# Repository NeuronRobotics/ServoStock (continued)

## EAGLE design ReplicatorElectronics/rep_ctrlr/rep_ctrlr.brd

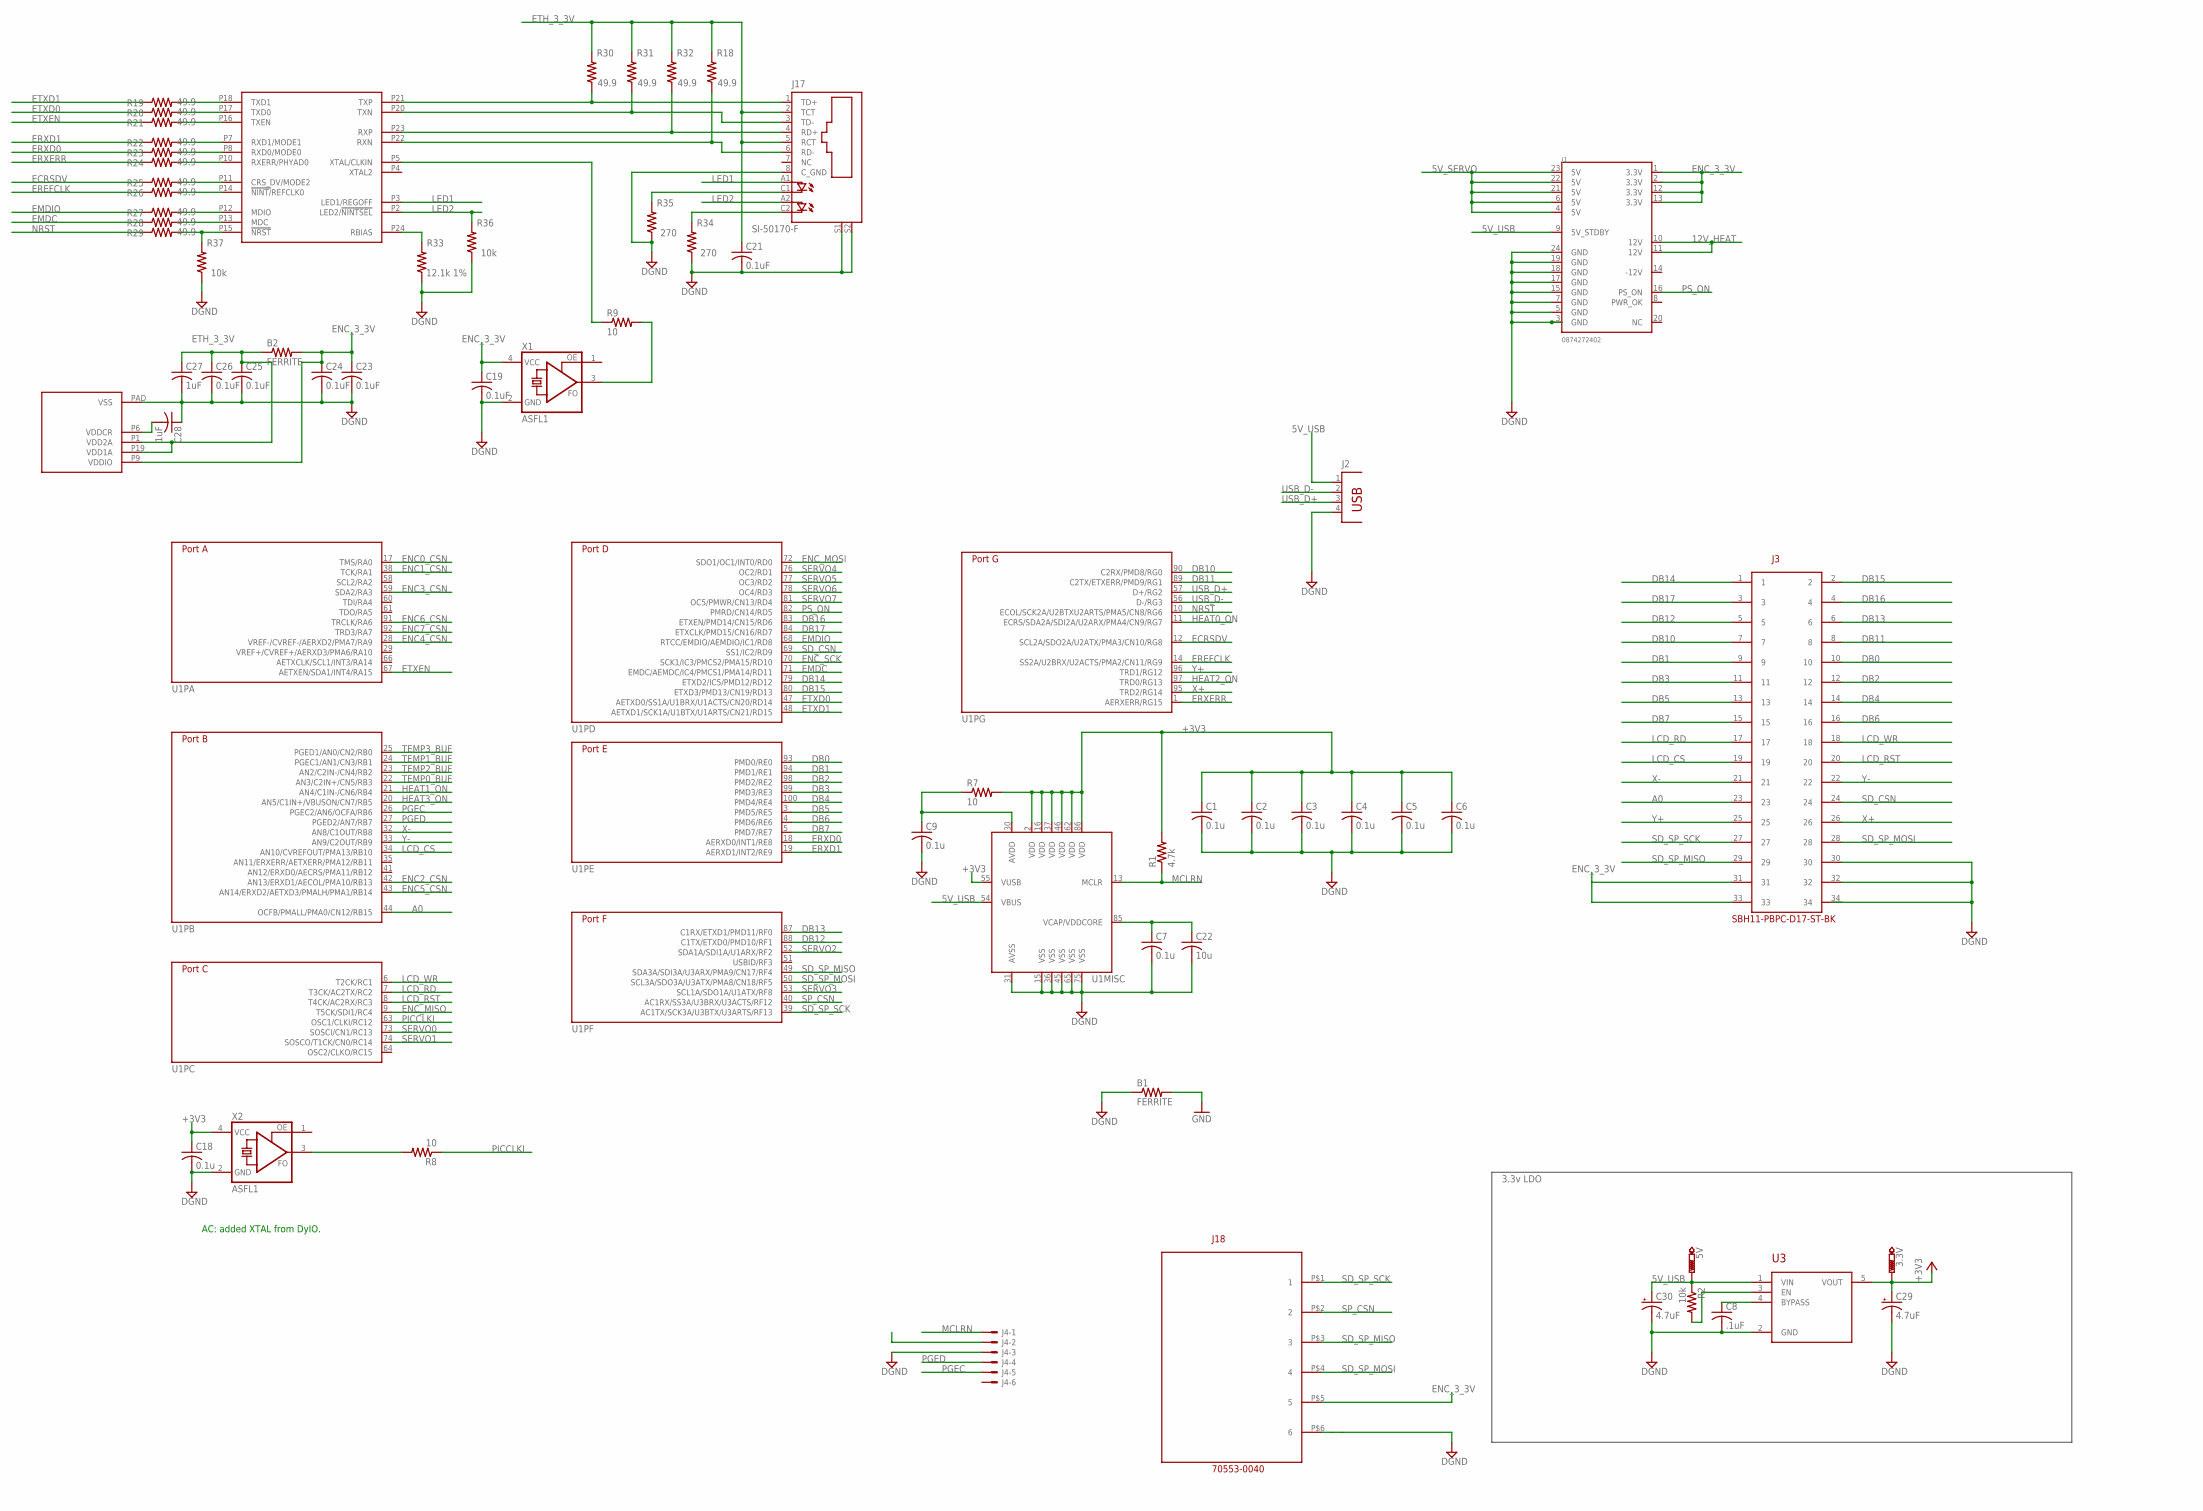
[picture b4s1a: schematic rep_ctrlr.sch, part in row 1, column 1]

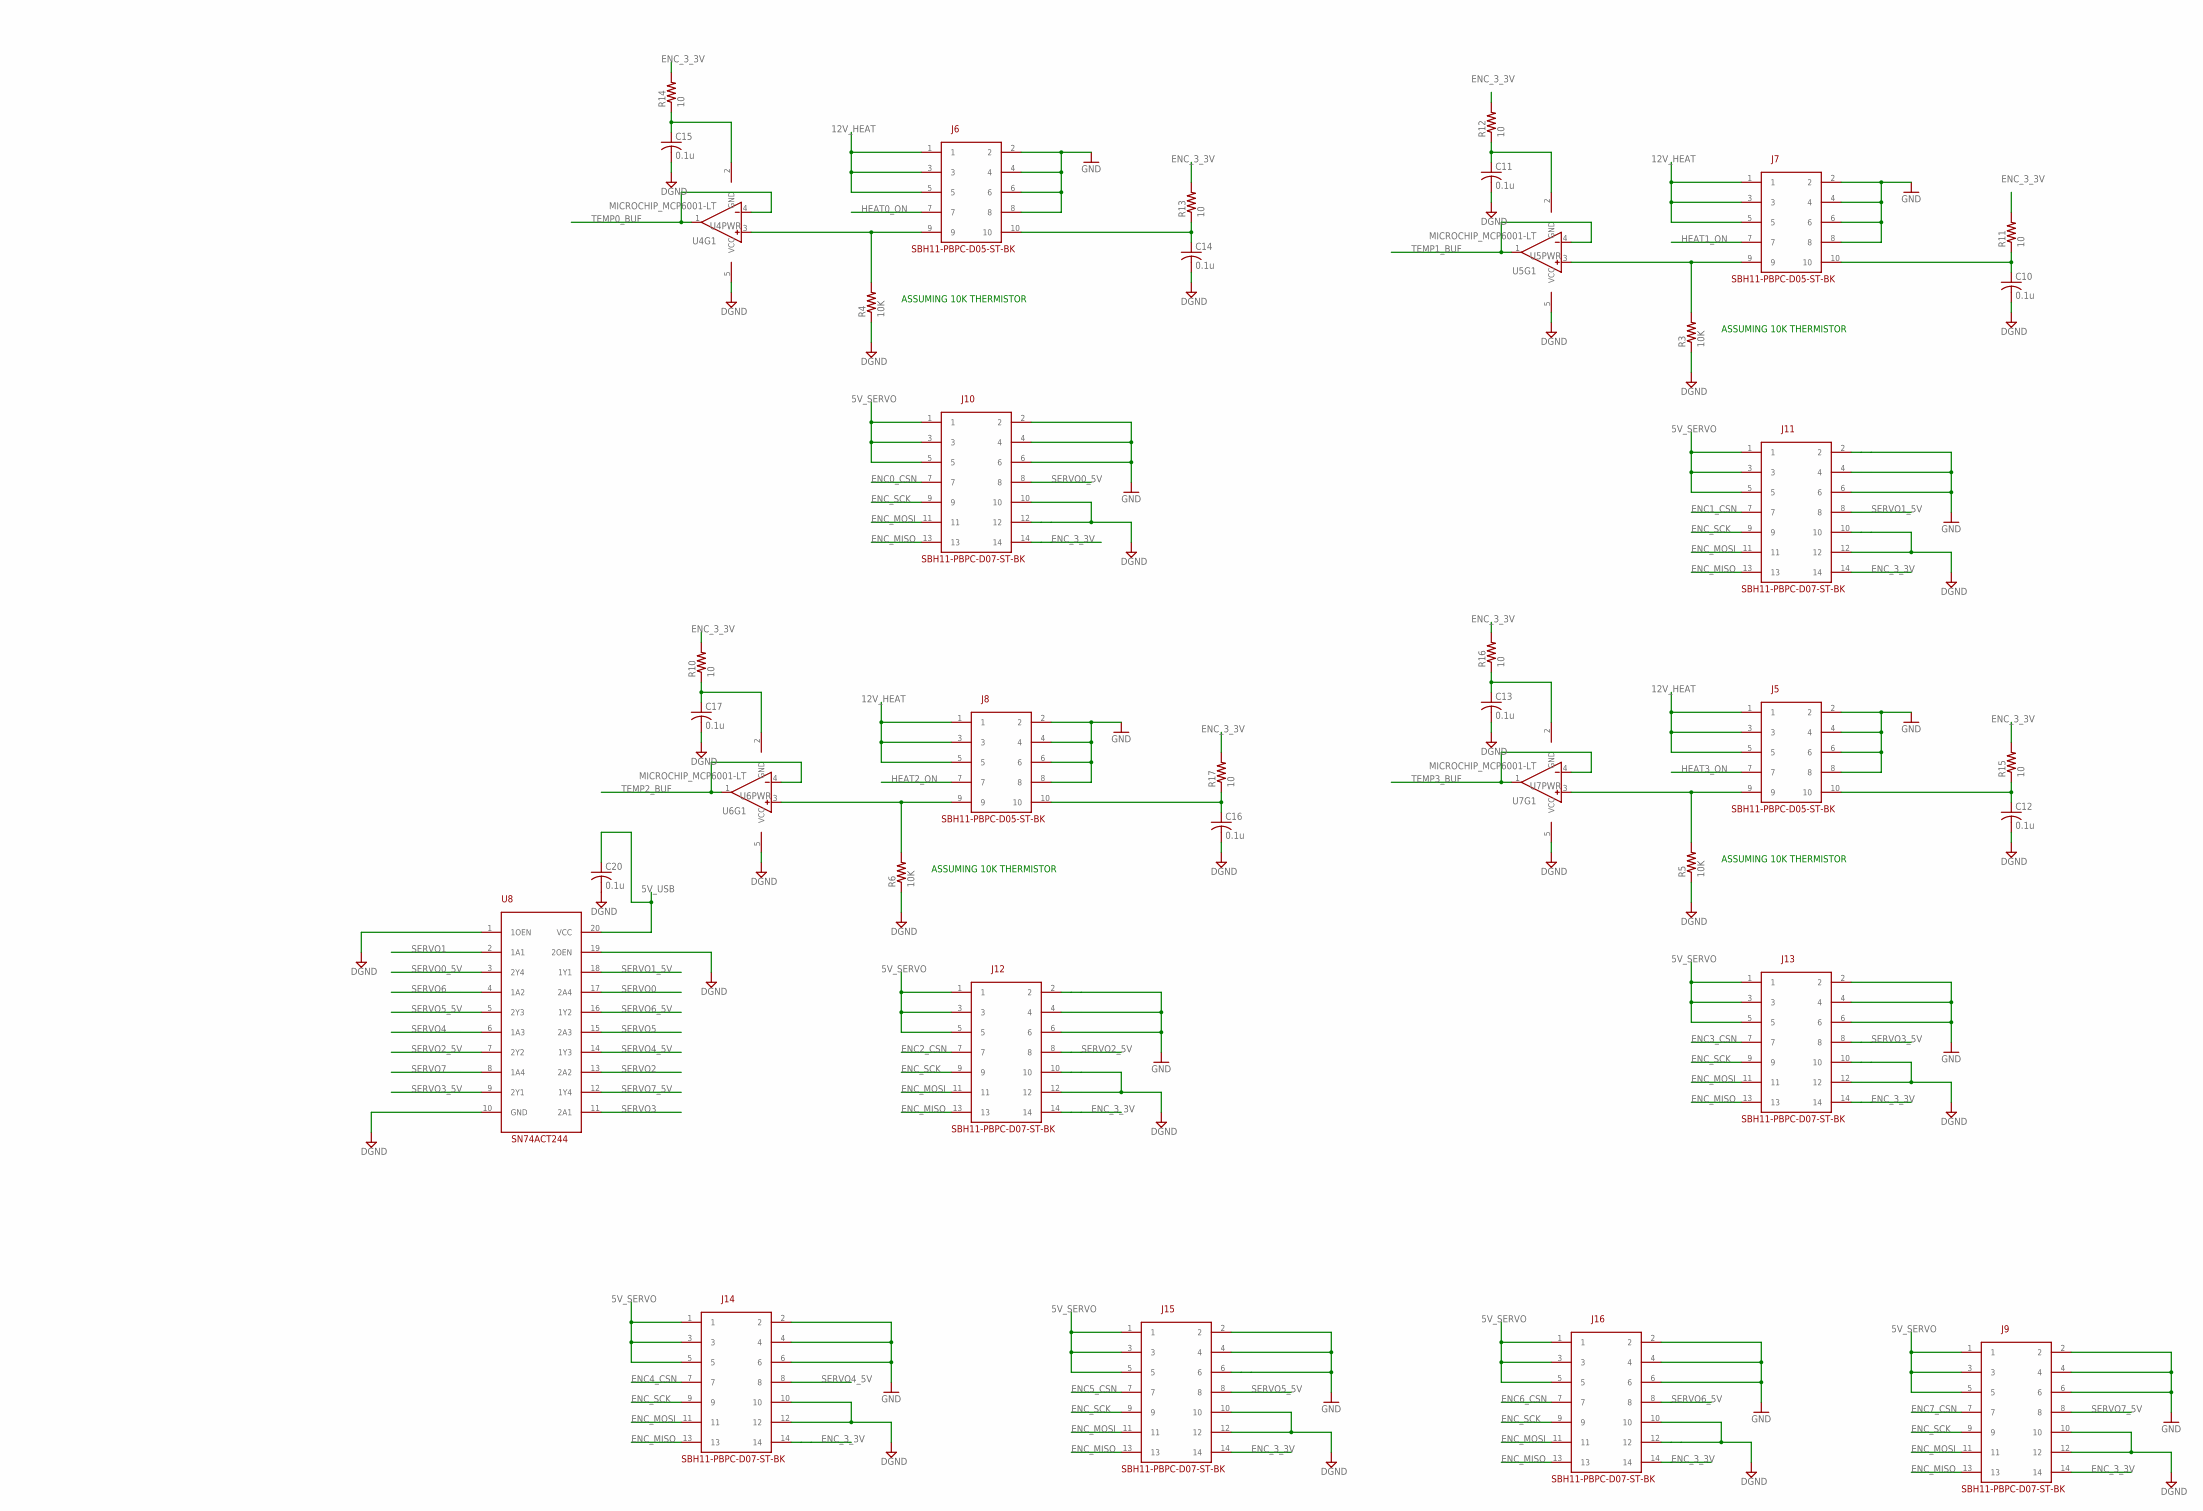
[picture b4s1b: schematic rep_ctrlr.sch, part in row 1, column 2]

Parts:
3.3V, 5V: PTR1TP14R; TP14R
B1, B2: FERRITE; R0805
C1, C2, C3, C4, C5, C6, C7, C9, C10, C11, C12, C13, C14, C15, C16, C17, C18, C20: 0.1u; C0402
C8: .1uF; C0402@1
C19, C21: 0.1uF; C0402
C22: 10u; C0603
C23, C24, C25, C26: 0.1uF; C0603
C27, C28: 1uF; C0603
C29, C30: 4.7uF; R/2012-12R
J1: 0874272402; ATX24_RIGHT_ANGLE
J2: PN61729
J3: SBH11-PBPC-D17-ST-BK
J4: 22-23-2061
J5, J6, J7, J8: SBH11-PBPC-D05-ST-BK
J9, J10, J11, J12, J13, J14, J15, J16: SBH11-PBPC-D07-ST-BK
J17: SI-50170-F; SI-50170
J18: 70553-0106; 70553-0109
R1: 4.7k; R0402
R2: 10k; R0402
R3, R4, R5, R6: 10K; R0402
R7, R8, R9, R10, R11, R12, R13, R14, R15, R16, R17: 10; R0402
R18, R19, R20, R21, R22, R23, R24, R25, R26, R27, R28, R29, R30, R31, R32: 49.9; R0603
R33: 12.1k 1%; R0603
R34, R35: 270; R0603
R36, R37: 10k; R0603
U1: MICROCHIP_PIC32MX7X5F256L-PF; MICROCHIP_TQ100-PF
U2: 8720A_PHY; QFN24
U3: LDS3985XX33; SOT23-5
U4, U5, U6, U7: MICROCHIP_MCP6001-LT; MICROCHIP_SC70-5-LT
U8: SN74ACT244; 20-SOIC
X1, X2: ASFL1; ASF

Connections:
5V_SERVO: J1.4 (5V), J1.6 (5V), J1.21 (5V), J1.22 (5V), J1.23 (5V), J9.1, J9.3, J9.5, J10.1, J10.3, J10.5, J11.1, J11.3, J11.5, J12.1, J12.3, J12.5, J13.1, J13.3, J13.5, J14.1, J14.3, J14.5, J15.1, J15.3, J15.5, J16.1, J16.3, J16.5
5V_USB: 5V.TP, C20.1, C30.+, J1.9 (5V_STDBY), J2.1, R2.1, U1.54 (VBUS), U3.1 (VIN), U8.20 (VCC)
12V_HEAT: J1.10 (12V), J1.11 (12V), J5.1, J5.3, J5.5, J6.1, J6.3, J6.5, J7.1, J7.3, J7.5, J8.1, J8.3, J8.5
+3V3: 3.3V.TP, C1.1, C2.1, C3.1, C4.1, C5.1, C6.1, C18.1, C29.+, J4.2, R1.2, R7.2, U1.2 (VDD), U1.16 (VDD), U1.37 (VDD), U1.46 (VDD), U1.55 (VUSB), U1.62 (VDD), U1.86 (VDD), U3.5 (VOUT), X2.4 (VCC)
A0: J3.23, U1.44 (OCFB/PMALL/PMA0/CN12/RB15)
DB0: J3.10, U1.93 (PMD0/RE0)
DB1: J3.9, U1.94 (PMD1/RE1)
DB2: J3.12, U1.98 (PMD2/RE2)
DB3: J3.11, U1.99 (PMD3/RE3)
DB4: J3.14, U1.100 (PMD4/RE4)
DB5: J3.13, U1.3 (PMD5/RE5)
DB6: J3.16, U1.4 (PMD6/RE6)
DB7: J3.15, U1.5 (PMD7/RE7)
DB10: J3.7, U1.90 (C2RX/PMD8/RG0)
DB11: J3.8, U1.89 (C2TX/ETXERR/PMD9/RG1)
DB12: J3.5, U1.88 (C1TX/ETXD0/PMD10/RF1)
DB13: J3.6, U1.87 (C1RX/ETXD1/PMD11/RF0)
DB14: J3.1, U1.79 (ETXD2/IC5/PMD12/RD12)
DB15: J3.2, U1.80 (ETXD3/PMD13/CN19/RD13)
DB16: J3.4, U1.83 (ETXEN/PMD14/CN15/RD6)
DB17: J3.3, U1.84 (ETXCLK/PMD15/CN16/RD7)
DGND: B1.1, C1.2, C2.2, C3.2, C4.2, C5.2, C6.2, C7.2, C8.2, C9.2, C10.2, C11.2, C12.2, C13.2, C14.2, C15.2, C16.2, C17.2, C18.2, C19.2, C20.2, C21.2, C22.2, C23.2, C24.2, C25.2, C26.2, C27.2, C28.1, C29.-, C30.-, J1.3 (GND), J1.5 (GND), J1.7 (GND), J1.15 (GND), J1.17 (GND), J1.18 (GND), J1.19 (GND), J1.24 (GND), J2.4, J3.30, J3.32, J4.3, J9.10, J9.12, J10.10, J10.12, J11.10, J11.12, J12.10, J12.12, J13.10, J13.12, J14.10, J14.12, J15.10, J15.12, J16.10, J16.12, J17.8 (C_GND), J17.S1, J17.S2, J18.P$6 (6), R3.1, R4.1, R5.1, R6.1, R33.1, R34.1, R35.1, R36.1, R37.1, U1.15 (VSS), U1.31 (AVSS), U1.36 (VSS), U1.45 (VSS), U1.65 (VSS), U1.75 (VSS), U2.PAD (VSS), U3.2 (GND), U4.5 (VCC), U5.5 (VCC), U6.5 (VCC), U7.5 (VCC), U8.1 (1OEN), U8.10 (GND), U8.19 (2OEN), X1.2 (GND), X2.2 (GND)
ECRSDV: R25.1, U1.12 (SCL2A/SDO2A/U2ATX/PMA3/CN10/RG8)
EMDC: R28.1, U1.71 (EMDC/AEMDC/IC4/PMCS1/PMA14/RD11)
EMDIO: R27.1, U1.68 (RTCC/EMDIO/AEMDIO/IC1/RD8)
ENC0_CSN: J10.7, U1.17 (TMS/RA0)
ENC1_CSN: J11.7, U1.38 (TCK/RA1)
ENC2_CSN: J12.7, U1.42 (AN13/ERXD1/AECOL/PMA10/RB13)
ENC3_CSN: J13.7, U1.59 (SDA2/RA3)
ENC4_CSN: J14.7, U1.28 (VREF-/CVREF-/AERXD2/PMA7/RA9)
ENC5_CSN: J15.7, U1.43 (AN14/ERXD2/AETXD3/PMALH/PMA1/RB14)
ENC6_CSN: J16.7, U1.91 (TRCLK/RA6)
ENC7_CSN: J9.7, U1.92 (TRD3/RA7)
ENC_3_3V: B2.2, C19.1, C23.1, C24.1, J1.1 (3.3V), J1.2 (3.3V), J1.12 (3.3V), J1.13 (3.3V), J3.31, J3.33, J9.14, J10.14, J11.14, J12.14, J13.14, J14.14, J15.14, J16.14, J18.P$5 (5), R10.2, R11.2, R12.2, R13.2, R14.2, R15.2, R16.2, R17.2, U2.P9 (VDDIO), X1.4 (VCC)
ENC_MISO: J9.13, J10.13, J11.13, J12.13, J13.13, J14.13, J15.13, J16.13, U1.9 (T5CK/SDI1/RC4)
ENC_MOSI: J9.11, J10.11, J11.11, J12.11, J13.11, J14.11, J15.11, J16.11, U1.72 (SDO1/OC1/INT0/RD0)
ENC_SCK: J9.9, J10.9, J11.9, J12.9, J13.9, J14.9, J15.9, J16.9, U1.70 (SCK1/IC3/PMCS2/PMA15/RD10)
EREFCLK: R26.1, U1.14 (SS2A/U2BRX/U2ACTS/PMA2/CN11/RG9)
ERXD0: R23.1, U1.18 (AERXD0/INT1/RE8)
ERXD1: R22.1, U1.19 (AERXD1/INT2/RE9)
ERXERR: R24.1, U1.1 (AERXERR/RG15)
ETH_3_3V: B2.1, C25.1, C26.1, C27.1, J17.2 (TCT), J17.5 (RCT), R18.2, R30.2, R31.2, R32.2, U2.P1 (VDD2A), U2.P19 (VDD1A)
ETXD0: R20.1, U1.47 (AETXD0/SS1A/U1BRX/U1ACTS/CN20/RD14)
ETXD1: R19.1, U1.48 (AETXD1/SCK1A/U1BTX/U1ARTS/CN21/RD15)
ETXEN: R21.1, U1.67 (AETXEN/SDA1/INT4/RA15)
GND: B1.2, J5.2, J5.4, J5.6, J5.8, J6.2, J6.4, J6.6, J6.8, J7.2, J7.4, J7.6, J7.8, J8.2, J8.4, J8.6, J8.8, J9.2, J9.4, J9.6, J10.2, J10.4, J10.6, J11.2, J11.4, J11.6, J12.2, J12.4, J12.6, J13.2, J13.4, J13.6, J14.2, J14.4, J14.6, J15.2, J15.4, J15.6, J16.2, J16.4, J16.6
HEAT0_ON: J6.7, U1.11 (ECRS/SDA2A/SDI2A/U2ARX/PMA4/CN9/RG7)
HEAT1_ON: J7.7, U1.21 (AN4/C1IN-/CN6/RB4)
HEAT2_ON: J8.7, U1.97 (TRD0/RG13)
HEAT3_ON: J5.7, U1.20 (AN5/C1IN+/VBUSON/CN7/RB5)
LCD_CS: J3.19, U1.34 (AN10/CVREFOUT/PMA13/RB10)
LCD_RD: J3.17, U1.7 (T3CK/AC2TX/RC2)
LCD_RST: J3.20, U1.8 (T4CK/AC2RX/RC3)
LCD_WR: J3.18, U1.6 (T2CK/RC1)
LED1: J17.A1 (A), U2.P3 (LED1/REGOFF)
LED2: J17.A2 (A1), R36.2, U2.P2 (LED2/!NINTSEL)
MCLRN: J4.1, R1.1, U1.13 (MCLR)
unnamed: R8.2, X2.3 (FO)
unnamed: C9.1, R7.1, U1.30 (AVDD)
unnamed: R9.2, X1.3 (FO)
unnamed: C7.1, C22.1, U1.85 (VCAP/VDDCORE)
unnamed: J7.9, R3.2, U5.3 (IN+)
unnamed: J5.9, R5.2, U7.3 (IN+)
unnamed: C12.1, J5.10, R15.1
unnamed: C10.1, J7.10, R11.1
unnamed: C11.1, R12.1, U5.2 (GND)
unnamed: C13.1, R16.1, U7.2 (GND)
unnamed: J6.9, R4.2, U4.3 (IN+)
unnamed: C14.1, J6.10, R13.1
unnamed: C15.1, R14.1, U4.2 (GND)
unnamed: J8.9, R6.2, U6.3 (IN+)
unnamed: C16.1, J8.10, R17.1
unnamed: C17.1, R10.1, U6.2 (GND)
unnamed: R19.2, U2.P18 (TXD1)
unnamed: R20.2, U2.P17 (TXD0)
unnamed: R21.2, U2.P16 (TXEN)
unnamed: R22.2, U2.P7 (RXD1/MODE1)
unnamed: R23.2, U2.P8 (RXD0/MODE0)
unnamed: R24.2, U2.P10 (RXERR/PHYAD0)
unnamed: R25.2, U2.P11 (CRS_DV/MODE2)
unnamed: R26.2, U2.P14 (!NINT/!REFCLK0)
unnamed: R27.2, U2.P12 (MDIO)
unnamed: R28.2, U2.P13 (MDC)
unnamed: R29.2, R37.2, U2.P15 (!NRST)
unnamed: J17.1 (TD+), R30.1, U2.P21 (TXP)
unnamed: J17.3 (TD-), R31.1, U2.P20 (TXN)
unnamed: J17.4 (RD+), R32.1, U2.P23 (RXP)
unnamed: J17.6 (RD-), R18.1, U2.P22 (RXN)
unnamed: R9.1, U2.P5 (XTAL/CLKIN)
unnamed: R2.2, U3.3 (EN)
unnamed: C8.1, U3.4 (BYPASS)
unnamed: J17.C1 (C), R35.2
unnamed: J17.C2 (C1), R34.2
unnamed: C28.2, U2.P6 (VDDCR)
unnamed: R33.2, U2.P24 (RBIAS)
NRST: R29.1, U1.10 (ECOL/SCK2A/U2BTXU2ARTS/PMA5/CN8/RG6)
PGEC: J4.5, U1.26 (PGEC2/AN6/OCFA/RB6)
PGED: J4.4, U1.27 (PGED2/AN7/RB7)
PICCLKI: R8.1, U1.63 (OSC1/CLKI/RC12)
PS_ON: J1.16 (PS_ON), U1.82 (PMRD/CN14/RD5)
SD_CSN: J3.24, U1.69 (SS1/IC2/RD9)
SD_SP_MISO: J3.29, J18.P$3 (3), U1.49 (SDA3A/SDI3A/U3ARX/PMA9/CN17/RF4)
SD_SP_MOSI: J3.28, J18.P$4 (4), U1.50 (SCL3A/SDO3A/U3ATX/PMA8/CN18/RF5)
SD_SP_SCK: J3.27, J18.P$1 (1), U1.39 (AC1TX/SCK3A/U3BTX/U3ARTS/RF13)
SERVO0: U1.73 (SOSCI/CN1/RC13), U8.17 (2A4)
SERVO0_5V: J10.8, U8.3 (2Y4)
SERVO1: U1.74 (SOSCO/T1CK/CN0/RC14), U8.2 (1A1)
SERVO1_5V: J11.8, U8.18 (1Y1)
SERVO2: U1.52 (SDA1A/SDI1A/U1ARX/RF2), U8.13 (2A2)
SERVO2_5V: J12.8, U8.7 (2Y2)
SERVO3: U1.53 (SCL1A/SDO1A/U1ATX/RF8), U8.11 (2A1)
SERVO3_5V: J13.8, U8.9 (2Y1)
SERVO4: U1.76 (OC2/RD1), U8.6 (1A3)
SERVO4_5V: J14.8, U8.14 (1Y3)
SERVO5: U1.77 (OC3/RD2), U8.15 (2A3)
SERVO5_5V: J15.8, U8.5 (2Y3)
SERVO6: U1.78 (OC4/RD3), U8.4 (1A2)
SERVO6_5V: J16.8, U8.16 (1Y2)
SERVO7: U1.81 (OC5/PMWR/CN13/RD4), U8.8 (1A4)
SERVO7_5V: J9.8, U8.12 (1Y4)
SP_CSN: J18.P$2 (2), U1.40 (AC1RX/SS3A/U3BRX/U3ACTS/RF12)
TEMP0_BUF: U1.22 (AN3/C2IN+/CN5/RB3), U4.1 (OUT), U4.4 (IN-)
TEMP1_BUF: U1.24 (PGEC1/AN1/CN3/RB1), U5.1 (OUT), U5.4 (IN-)
TEMP2_BUF: U1.23 (AN2/C2IN-/CN4/RB2), U6.1 (OUT), U6.4 (IN-)
TEMP3_BUF: U1.25 (PGED1/AN0/CN2/RB0), U7.1 (OUT), U7.4 (IN-)
USB_D+: J2.3, U1.57 (D+/RG2)
USB_D-: J2.2, U1.56 (D-/RG3)
X+: J3.26, U1.95 (TRD2/RG14)
X-: J3.21, U1.32 (AN8/C1OUT/RB8)
Y+: J3.25, U1.96 (TRD1/RG12)
Y-: J3.22, U1.33 (AN9/C2OUT/RB9)

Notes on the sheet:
ASSUMING 10K THERMISTOR
AC: added XTAL from DyIO.
3.3v LDO

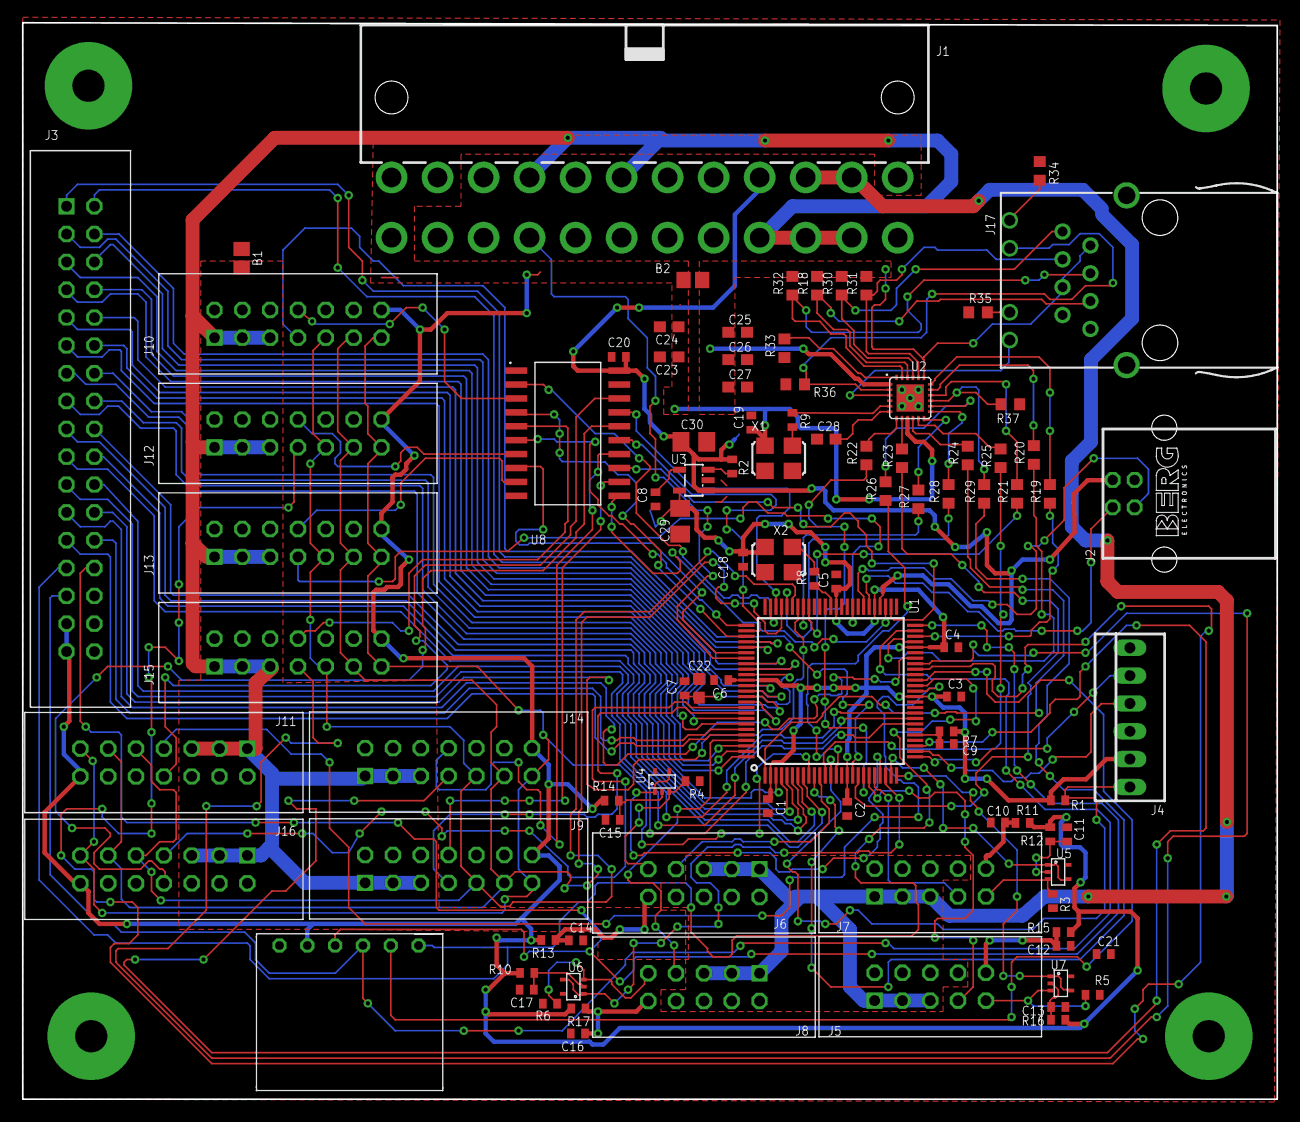
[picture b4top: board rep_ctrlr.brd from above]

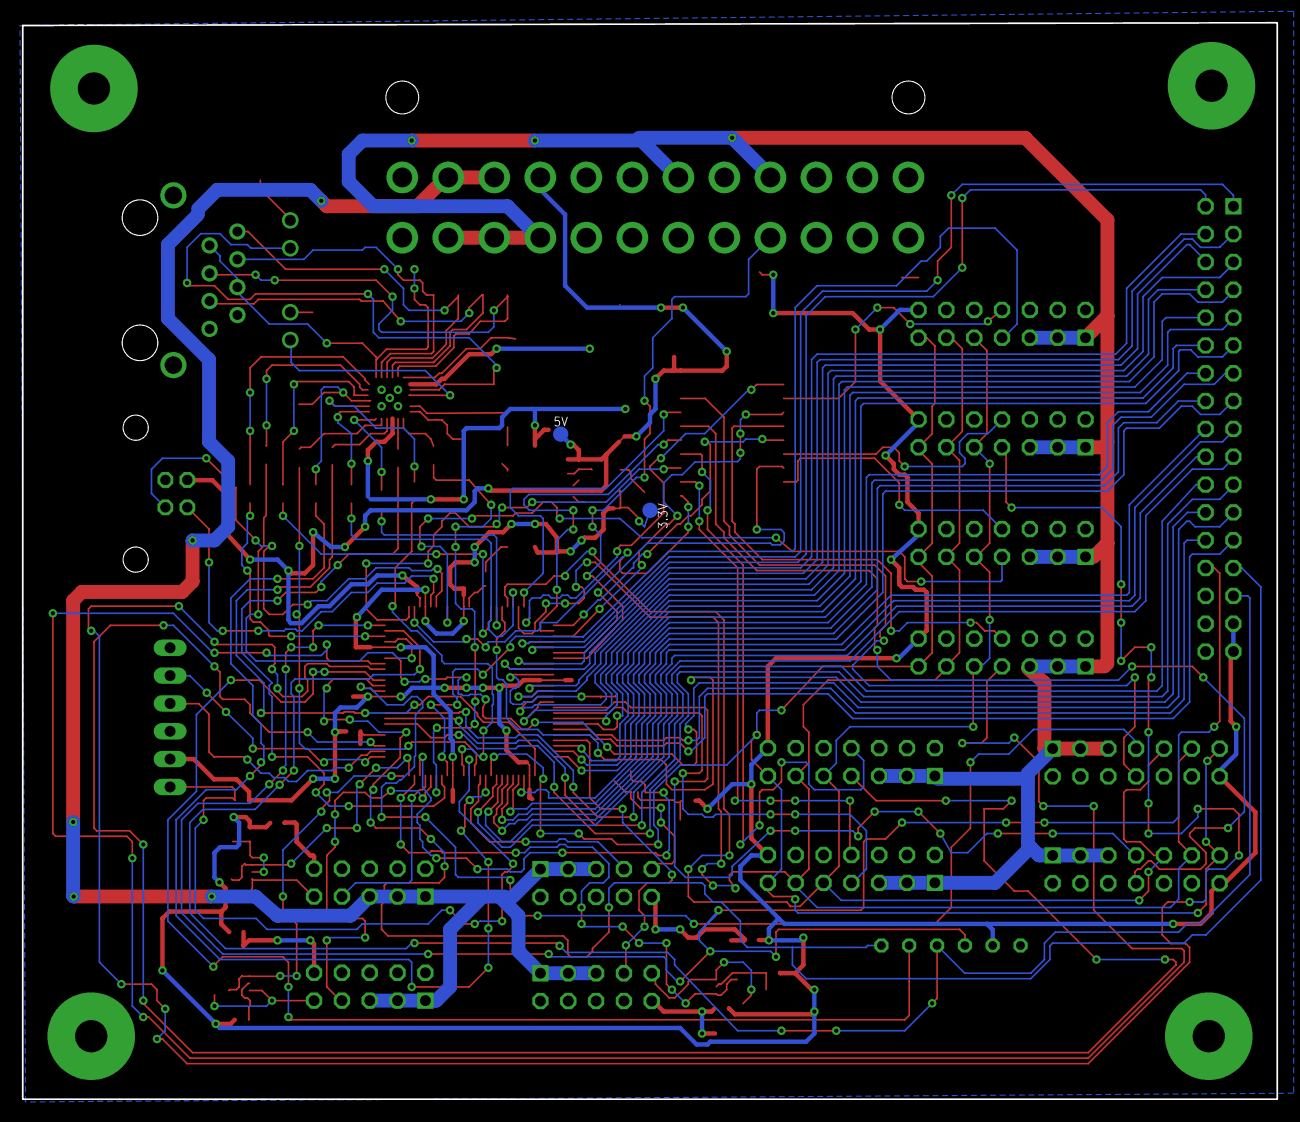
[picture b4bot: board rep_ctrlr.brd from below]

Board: 2 copper layers, 114.5 x 98.2 mm, 99 parts (2 on the bottom side), 131 nets.

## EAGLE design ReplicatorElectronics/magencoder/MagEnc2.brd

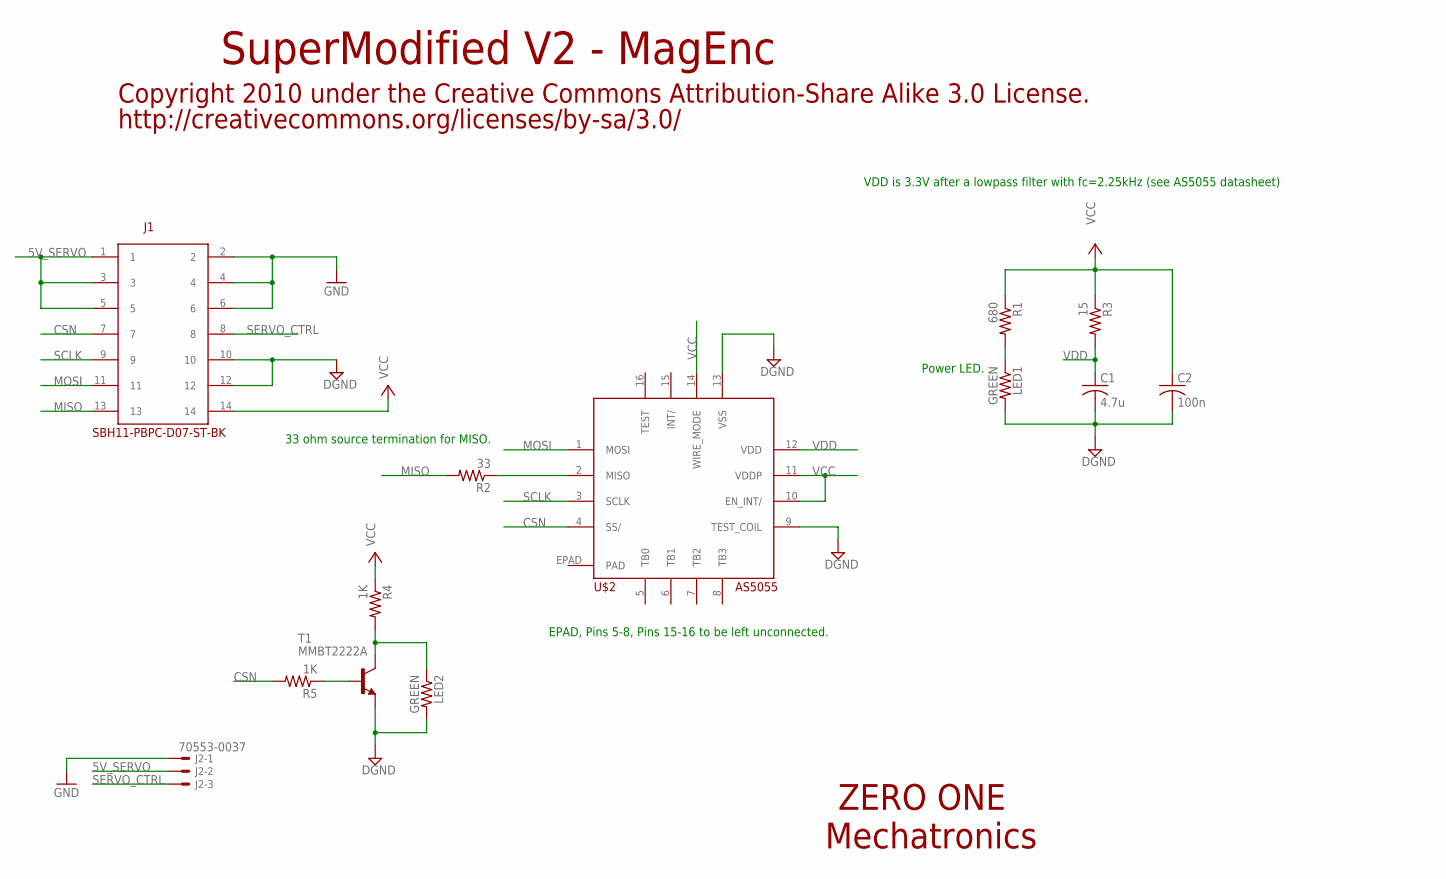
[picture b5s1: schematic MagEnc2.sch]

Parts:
C1: 4.7u; C0402
C2: 100n; C0402
J1: SBH11-PBPC-D07-ST-BK
J2: 70553-0037; 70553-03
LED1, LED2: GREEN; R0402
R1: 680; R0402
R2: 33; R0402
R3: 15; R0402
R4, R5: 1K; R0402
T1: MMBT2222A; SOT23-BEC
U$2: AS5055

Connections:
5V_SERVO: J1.1, J1.3, J1.5, J2.2
CSN: J1.7, R5.2, U$2.4 (SS/)
DGND: C1.2, C2.2, J1.10, J1.12, LED1.2, LED2.2, T1.E, U$2.9 (TEST_COIL), U$2.13 (VSS)
GND: J1.2, J1.4, J1.6, J2.1
MISO: J1.13, R2.2
MOSI: J1.11, U$2.1 (MOSI)
unnamed: LED1.1, R1.2
unnamed: LED2.1, R4.2, T1.C
unnamed: R5.1, T1.B
unnamed: R2.1, U$2.2 (MISO)
SCLK: J1.9, U$2.3 (SCLK)
SERVO_CTRL: J1.8, J2.3
VCC: C2.1, J1.14, R1.1, R3.1, R4.1, U$2.10 (EN_INT/), U$2.11 (VDDP), U$2.14 (WIRE_MODE)
VDD: C1.1, R3.2, U$2.12 (VDD)

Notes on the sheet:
ZERO ONE
Mechatronics
SuperModified V2 - MagEnc
Copyright 2010 under the Creative Commons Attribution-Share Alike 3.0 License.
http://creativecommons.org/licenses/by-sa/3.0/
VDD is 3.3V after a lowpass filter with fc=2.25kHz (see AS5055 datasheet)
EPAD, Pins 5-8, Pins 15-16 to be left unconnected.
33 ohm source termination for MISO.
Power LED.

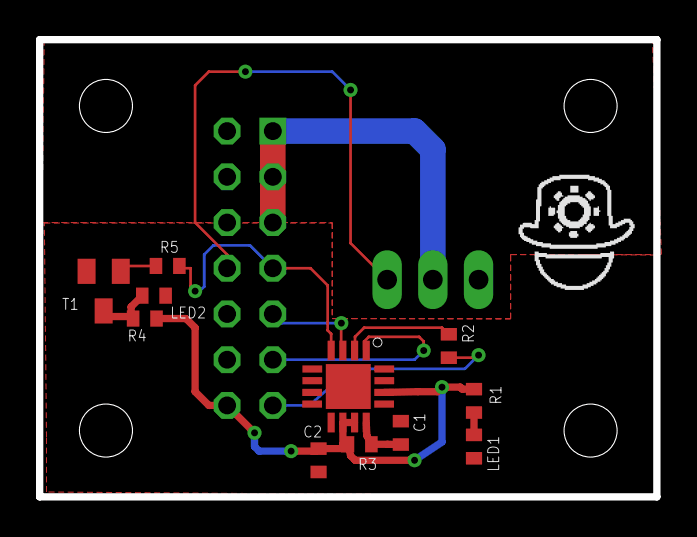
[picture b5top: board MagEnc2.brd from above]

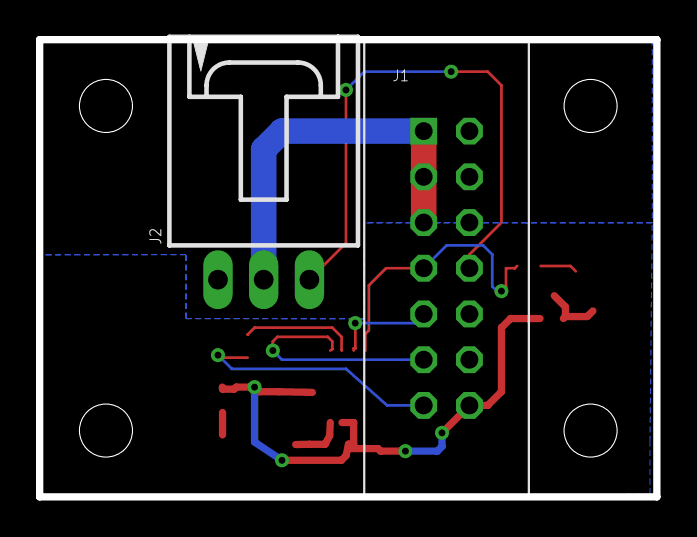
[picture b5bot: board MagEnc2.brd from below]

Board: 2 copper layers, 34.3 x 25.4 mm, 13 parts (2 on the bottom side), 14 nets.

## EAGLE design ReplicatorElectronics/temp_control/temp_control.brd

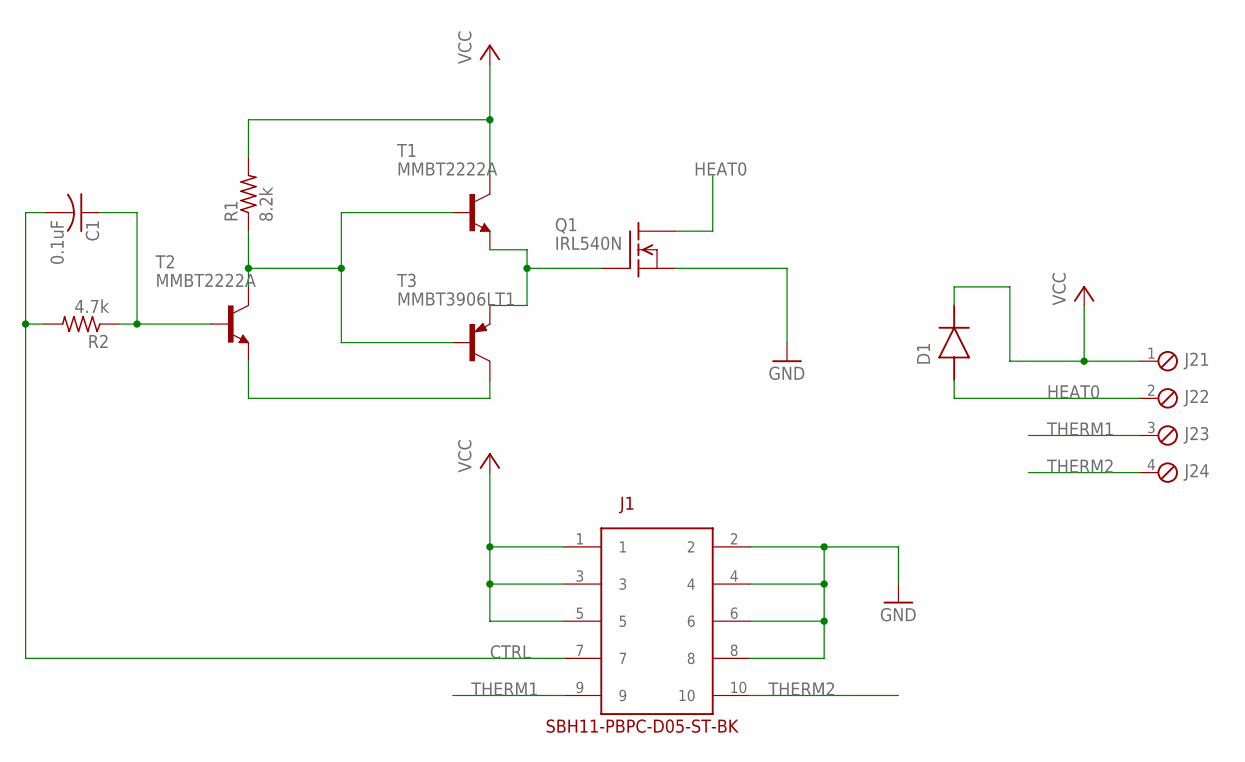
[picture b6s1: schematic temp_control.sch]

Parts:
C1: 0.1uF; C0603
D1: B340A-13-F; DISCRETE_SMA
J1: SBH11-PBPC-D05-ST-BK
J2: OSTVN04A150; 4POL254
Q1: IRL540N; TO220
R1: 8.2k; R0603
R2: 4.7k; R0603
T1, T2: MMBT2222A; SOT23-BEC
T3: MMBT3906LT1; SOT23-BEC

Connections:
CTRL: C1.2, J1.7, R2.2
GND: J1.2, J1.4, J1.6, J1.8, Q1.3 (S)
HEAT0: D1.A, J2.2, Q1.2 (D)
unnamed: C1.1, R2.1, T2.B
unnamed: R1.1, T1.B, T2.C, T3.B
unnamed: Q1.1 (G), T1.E, T3.E
unnamed: T2.E, T3.C
THERM1: J1.9, J2.3
THERM2: J1.10, J2.4
VCC: D1.C, J1.1, J1.3, J1.5, J2.1, R1.2, T1.C

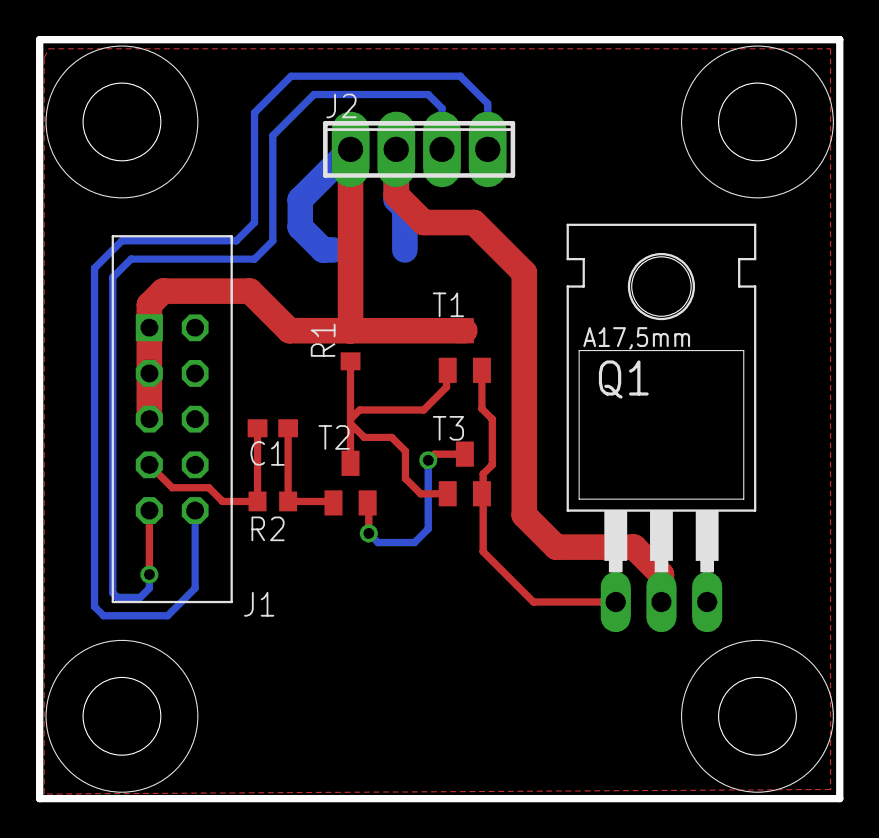
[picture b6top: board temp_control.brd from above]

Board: 2 copper layers, 44.5 x 42.2 mm, 10 parts (1 on the bottom side), 10 nets.

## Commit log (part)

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2012-08-23 servos and PID on interrupt
2012-08-23 Servo and PID working in ISR
2012-08-23 PID configs
2012-08-25 Encoder reset working
2012-08-30 working with arms attached
2012-09-05 faster servo and PID
2012-09-15 Servostruder update
2012-09-22 Changed names of several classes to ones that more accurately reflect the functionality. Added in ability to reorient model to rest on different faces. Added in ability to rotate model around y axis 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
2012-10-05 adding heaters
2012-10-10 =Inttrupt fix
2012-10-12 Tested volume estimating algorithm and it seems to be working. There is a degree of error that may be due to inconsistent use of float and double precision in different parts of the code.
2012-11-09 Kevins tester edits
2012-11-09 Printer working with temp and extrusion
2012-11-09 added the setpoint for extruder and heater
2012-11-09 derp
2012-11-11 convert to radian and back
2012-11-12 link limit tweak
2012-11-12 Calibrated so lowest reachable Z is 0
2012-11-12 =Cartesian in firmware
2012-11-17 About to run first test print
2012-11-17 making set tempreture wait
2012-11-17 Mild hack to get it printing before the parser is refactored to run line-by-line.
2012-11-17 Settings tweaks to stop thrashing the machine about.
2012-11-18 renamed
2012-11-30 calibrated temp
2012-12-13 =GCode parser error update
2012-12-21 No jReality yet. Major refactor to untangle the preview stuff into a better implemented MVC pattern. Divided STLPreviewCanvas3D and its supporting classes into model, view and controller packages. As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
2013-01-09 Made it log all encountered codes to file.
2013-02-10 2/10/13: Updated Encoder Board to include level translation. ~1 hour
2013-03-07 fixed file paths
2013-03-12 Added comments
2013-05-02 Changed the print statements
2013-05-09 Stable control loops again
2013-05-21 =Servo Calibration implementation
2013-06-11 Added auto-discovery of bowler RPC's
2013-06-14 Auto-parsing working for all data types
2013-11-10 I made it COMPACT\!
2013-11-11 Updated working on new board
2013-11-12 Working on the new board communications
2013-11-12 reorganized source tree
2013-11-12 Adding teh Kossel kinematics
2013-11-17 moving files
2013-11-20 Working Servostock motherboard
2013-11-24 Adding the new servo pin map
2013-11-25 some channels working
2013-11-27 All axis validated for ServoStock fw
2014-01-15 removed the inverse kinematics
2014-01-17 Renamed files and folders
    Renamed the files and folder to tier final locations
2014-01-18 Fixing the build paths
    Since the projects have been moved around i changed where the project
    files should expect to find the NR-Clib
2014-01-26 Change the data storage of sorted data into its own array
    This allows the position to stay constant through one servo cycle.
    Before this if a servo position was changed whail in a cycle, the sorted
    array would become unsorted.
2014-01-28 Remobing binary build files
2014-02-02 Changing the name of the code project
    This allows the hardware project to be imported.
2014-02-08 Adding the kinematics project
2014-02-08 Changed the license to BSD
2014-02-09 Updated the homing procedure to be modular
    I have moved the homing out of the bulk kinematics and into a joint
    level modularized updater.
2014-02-16 adding the printer driver layer to the NRSDK
2014-02-19 Adding the simple run square functiuon
2014-02-19 Direct control working
2014-02-19 Cartesian control working
2014-02-19 Updated the control gui
2014-02-19 Add more prints and the demo works, whatever...
2014-02-19 fixed the lower z bound
2014-02-19 More parametric startup
2014-02-19 final timeings for the demo
2014-02-27 Added the get all values statement in main loop
2014-02-27 Integrated the FK
2014-02-28 Fixing the linker step to inlude the math library
2014-02-28 Addign the servostock assembly instructiopns
2014-02-28 Referencing issue #1.
2014-03-01 yet another forward kinematics not working...
2014-03-01 Added back overlay with values
2014-03-01 overwrote image. Fixed.
2014-03-01 git now ignores eagle temp files
2014-03-01 Referencing issue #3.
2014-03-04 Intitial Checkin of repository
2014-03-06 Forward Kinematics were tested and worked as expected according to hand calculations. Inverse Kinematics were slightly off compared to the Javascript source file as noted in the KosselKinematics.c fi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
    Close #5
2014-03-06 I changed the bounds to match the robot's hardware.
2014-03-06 further refined robot bounds
2014-03-06 Added my name to the template. Jared Heiser #4
2014-03-07 Setting back up the interpolation stack for the Kinematics
2014-03-07 Moved function prototypes into the header
2014-03-09 Updated Test Case for 2-D Square to test both inverse and forward kinematics for the same example. Renamed function which updated the main .c file.
2014-03-13 Added test cases around boundaries of workspace of the robot. Added test case for 2-D circle with 4 points.
    Added geneirc test case function which takes in any set of data points.
2014-03-16 Testing new billcalabro account link
2014-03-16 Close #2
    Made a comment at the top where I added my name to the author's list.
2014-03-17 Close #10
2014-03-17 First step of importing Bill's Inverse Velocity Kinematic calculation function. Removed typo from RBE501-2014-Delta-Kinematics.c
    Issue #14
2014-03-17 Delete MatlabScript.md~
    Accidentally added byproduct of gedit with MatlabScript.md text file, Issue #14
2014-03-18 Added more specific TODO's in the 'servostock_velInverse' function based on Matlab notes. Updated parameter list to 'servostock_velInverse' function.
2014-03-19 Further manipulation of TODO comments to implementation of servostock_velInverse in preparation for team meeting, in reference to Issue #14.
2014-03-20 Fixed a few minor typos found by Mike, in reference to Issue #14.
2014-03-20 Added print actions to script to get individual jacobian entries for C-code, in reference to Issue #14.
2014-03-21 Fixed a few more typos in the Matlab Model. It is still not giving good data, though now it is extremely small, rather than extremely large. In reference to Issue #14.
2014-03-23 Michael DiBlasi Updated Forward Velocity Kinematics function in KosselKinematics.c from latest matlab script. Issue #14
2014-04-03 Workes without the twitching
2014-04-05 Michael DiBlasi - Added SystemFlow.txt. Deleted SystemFlow.pdf. Close Issue #21.
2014-04-05 Michael DiBlasi - Added System Flow chart to SystemFlow document. Close Issue #20.
2014-04-08 Tuned PID controller and slowed down the task space interpolation
2014-04-08 Michael DiBlasi - Added System Flowchart and properly commented commit. Close #20
2014-04-11 Converted Matlab script into C Code, see 'formJacobian' of 'KosselKinematics.c', and configured both forward and inverse velocity functions. Basic test cases show that forward match Matlab simulation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
2014-04-12 Added the storage to flash of the configurations
2014-04-13 Added another Matlab generated function, 'formInvJacobian', and removed manual method for pseudo-inverse. Now both forward and inverse velocity kinematics match the test case from Matlab within a few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
2014-04-13 Added further test cases to evaluate C Code against Matlab simulation. This is in reference to Issue #19.
2014-04-22 Close Issue #15, Issue #16, and Issue #17 for Krishna as he is still unable to get Github working.
2014-04-23 remover junk prototype object
2014-04-23 Added the link provider calls for the cartesian controller
2014-04-26 More stable interpolation system
2014-04-29 Added robot configuration parameters to velocity kinematics and related test cases. Added explicit parameter for angle length in elipse test case (used for maximum workspace). Updated Matlab to inclu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
2014-04-29 Close #22 - This was closed by adding the Delta Robot Write-up _ver2.pdf file to the project which consists of our approach to the project, goals, and conclusion.
2014-04-30 Referencing the c-bowler project rather than the files
2014-05-03 Adding the firmware build instructions
2014-05-07 Adding the frog leg kinematics
2014-05-07 initial calculations
2014-05-07 .project update
2014-05-07 Frog Leg kinematics added to the ServoStock board
2014-05-07 Finished integrating the frog leg kinematics
2014-05-08 tweaking the encoders
2014-05-23 Tuned kimematics to arm
2014-06-02 adding the dependancies
2014-06-06 Made the encoders not work any more...
2014-06-12 Config file updates
2014-06-13 Fixing the wrap over by not reading the raw value untill its a full read.
2014-06-13 making the compile pedantic
2014-06-14 running without data curruption
2014-06-15 Changing the PID datable request
2014-06-16 Startup sequence working
2014-07-08 stubs for cartesian interface
2014-07-08 fixed the joint vector override
2014-08-04 adding the complex math functions to the Jacobian
2014-08-11 Changing the c-bowler library location
2014-08-12 looking for the null pointer in the servostock code
2014-08-18 Adding the configuration files
2014-08-19 Changing the types in the c-bowler stack to stdint with boolean
2014-08-19 Adding a pointer based PID interface
2014-08-20 Testing the task space interpolation
2014-08-20 Tuned task space controller
2014-08-21 Fixed the offset of the variables to the fixed point scaling
2014-08-25 removing useless prints
2014-08-29 Adding a feed override layer to the linear moves
2014-08-29 removing unused files
2014-08-29 added the pause print ffeature
2014-08-29 added the set and get configurations for the state based controller
2014-08-29 chack the homing based on the homing switch
2014-08-29 interface to homing procedue now running
2014-08-30 Adding the coms layer for the configuratuions
2014-08-30 Changing the datatype for the pause to a booelan
2014-09-03 changing the configuration defaults
2014-09-04 setLED function sets LED color.
2014-09-06 Adding the roling average filter for the encoder read
2014-09-06 Removing legacy folders
2014-09-06 Removing prints in async
2014-09-07 rolling back the rolling average filter
2014-09-07 Switched the Servo IO manipulations to atomic set/clear
2014-09-07 Fixing all of the rest of the IO manipulations
2014-09-07 Simplified IO set interface
2014-09-07 Fixed teh Rev4 definitions
2014-09-07 Rolling average filter to the position read
2014-09-09 updating the kinematics mapping system
2014-09-09 Settuing and geting the kinematics math index now in protocol
2014-09-09 Added the link mapping configuration set command processor
2014-09-09 ehsures the servostock kinematics is the default
2014-09-10 Fixed the slicer packet size
2014-09-11 re enabled heaters
2014-09-12 Adding the get pause state function
2014-09-12 work on the heater sub-system
2014-09-12 Adding the hardPositioning parameter
2014-09-13 mapping hacked to work. PWM works. PIDs just fine.
2014-09-13 removing the led heater system
2014-09-13 remove commented code
2014-09-17 extruder changes per rev
2014-10-28 switching rpcs back to statics
2014-10-30 removing prints
2014-10-31 adding the string to packet loading
2014-10-31 removing static memory in favor of global memory space
2015-02-20 Fixing maseter to adhere to c-bowler standards
2015-02-20 adding the build to bootloader configuration
2015-02-20 adding alternate builds
2015-02-21 Bootloader now working Adding the board specific builds
2015-05-15 adding the rev3 bootloader directive
